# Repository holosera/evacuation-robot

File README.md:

evacuation-robot
================

Robot for automated evacuation of exetainer vials used in research.

Frame (acrylic sheets)

3d Printed mechanical parts 

Custom electronics (pcb and schematics)

Additional parts list

Filetypes:
.scad -> Openscad

.svg -> Inkscape

.ino -> Arduino IDE

.dxf -> Inkscape

.stl -> Meshlab

.brd -> Eagle

.sch -> Eagle

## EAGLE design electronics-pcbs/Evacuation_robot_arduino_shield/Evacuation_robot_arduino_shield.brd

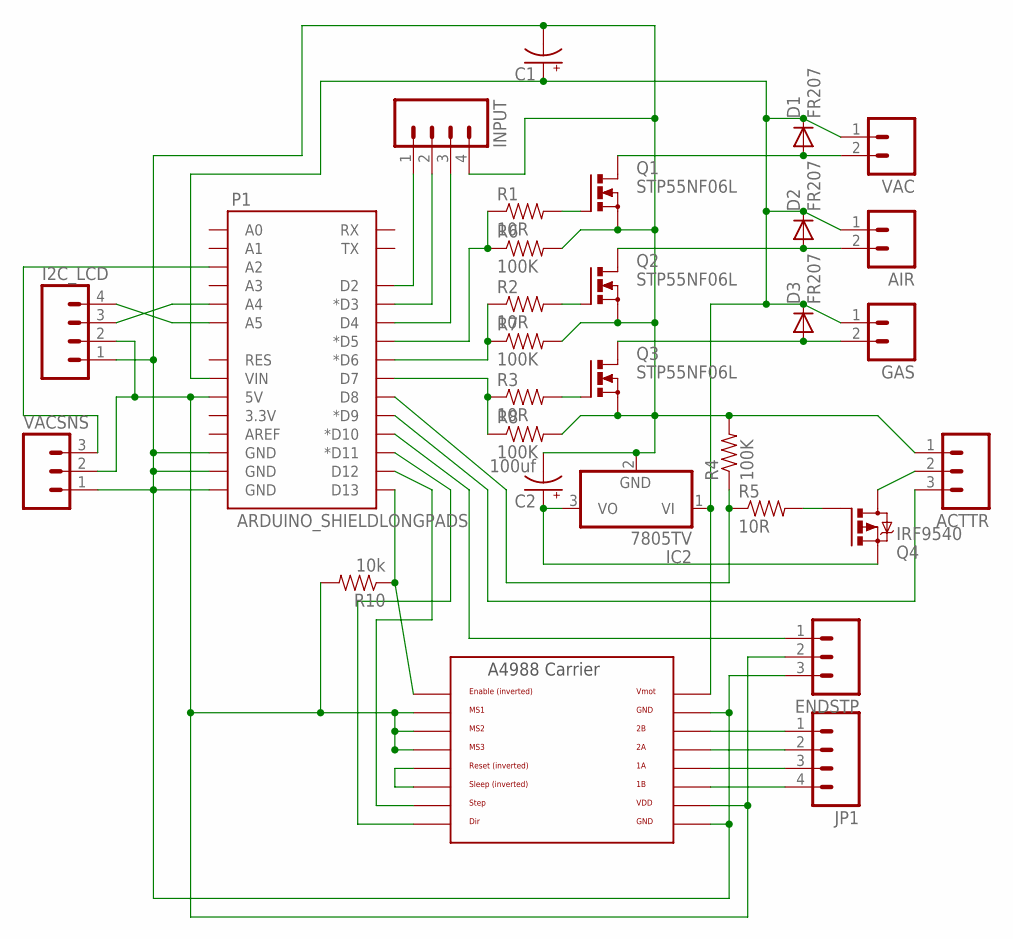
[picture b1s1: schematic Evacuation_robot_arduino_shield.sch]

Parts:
ACTTR: M03LONGPADS; 1X03_LONGPADS
AIR: M02PTH3; 1X02_LONGPADS
C1: CAP_POLPTH4; CPOL-RADIAL-1000UF-25V
C2: 100uf; CPOL-RADIAL-100UF-25V
D1, D2, D3: FR207; DIODE-1N4148
ENDSTP: M03LONGPADS; 1X03_LONGPADS
GAS: M02PTH3; 1X02_LONGPADS
I2C_LCD: M04LONGPADS; 1X04_LONGPADS
IC2: 7805TV; TO220V
INPUT: M04LONGPADS; 1X04_LONGPADS
JP1: M04LONGPADS; 1X04_LONGPADS
P1: ARDUINO_SHIELDLONGPADS; DUEMILANOVE_SHIELD_LONGPADS
Q1, Q2, Q3: STP55NF06L; TO220BV
Q4: IRF9540; TO220BV
R1, R2, R3, R5: 10R; AXIAL-0.3
R4, R6, R7, R8: 100K; AXIAL-0.3
R10: 10k; AXIAL-0.3
U$1: A4988BREAKOUT
VAC: M02PTH3; 1X02_LONGPADS
VACSNS: M03LONGPADS; 1X03_LONGPADS

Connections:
unnamed: INPUT.3, P1.D4
unnamed: INPUT.2, P1.D3 (*D3)
unnamed: P1.D6 (*D6), R2.P$1 (1), R7.P$1 (1)
unnamed: P1.D7, R3.P$1 (1), R8.P$1 (1)
unnamed: P1.D5 (*D5), R1.P$1 (1), R6.P$1 (1)
unnamed: ENDSTP.1, P1.D10 (*D10)
unnamed: Q1.G, R1.P$2 (2)
unnamed: JP1.1, U$1.2B
unnamed: INPUT.1, P1.D2
unnamed: Q3.G, R3.P$2 (2)
unnamed: Q2.G, R2.P$2 (2)
unnamed: D1.A, Q1.D, VAC.2
unnamed: AIR.2, D2.A, Q2.D
unnamed: D3.A, GAS.2, Q3.D
unnamed: I2C_LCD.3, P1.A4
unnamed: JP1.2, U$1.2A
unnamed: I2C_LCD.4, P1.A5
unnamed: AIR.1, C1.1 (+), D1.C, D2.C, D3.C, GAS.1, IC2.1 (VI), P1.VIN, U$1.VMOT, VAC.1
unnamed: JP1.3, U$1.1A
unnamed: JP1.4, U$1.1B
unnamed: U$1.RST, U$1.SLP (SLEEP)
unnamed: ACTTR.3, P1.D9 (*D9)
unnamed: Q4.G, R5.P$2 (2)
unnamed: P1.D13, R10.P$1 (1), U$1.EN
unnamed: P1.D11 (*D11), U$1.DIR
unnamed: P1.D8, R4.P$1 (1), R5.P$1 (1)
unnamed: P1.A2, VACSNS.3
unnamed: C2.1 (+), IC2.3 (VO), Q4.S
unnamed: P1.D12, U$1.STEP
unnamed: ACTTR.2, Q4.D
unnamed: ENDSTP.2, I2C_LCD.2, P1.5V, R10.P$2 (2), U$1.MS1, U$1.MS2, U$1.MS3, U$1.VDD, VACSNS.2
unnamed: ACTTR.1, C1.2 (-), C2.2 (-), ENDSTP.3, I2C_LCD.1, IC2.2 (GND), INPUT.4, P1.GND@0 (GND), P1.GND@1 (GND), P1.GND@2 (GND), Q1.S, Q2.S, Q3.S, R4.P$2 (2), R6.P$2 (2), R7.P$2 (2), R8.P$2 (2), U$1.GND, U$1.GND@0 (GND), VACSNS.1

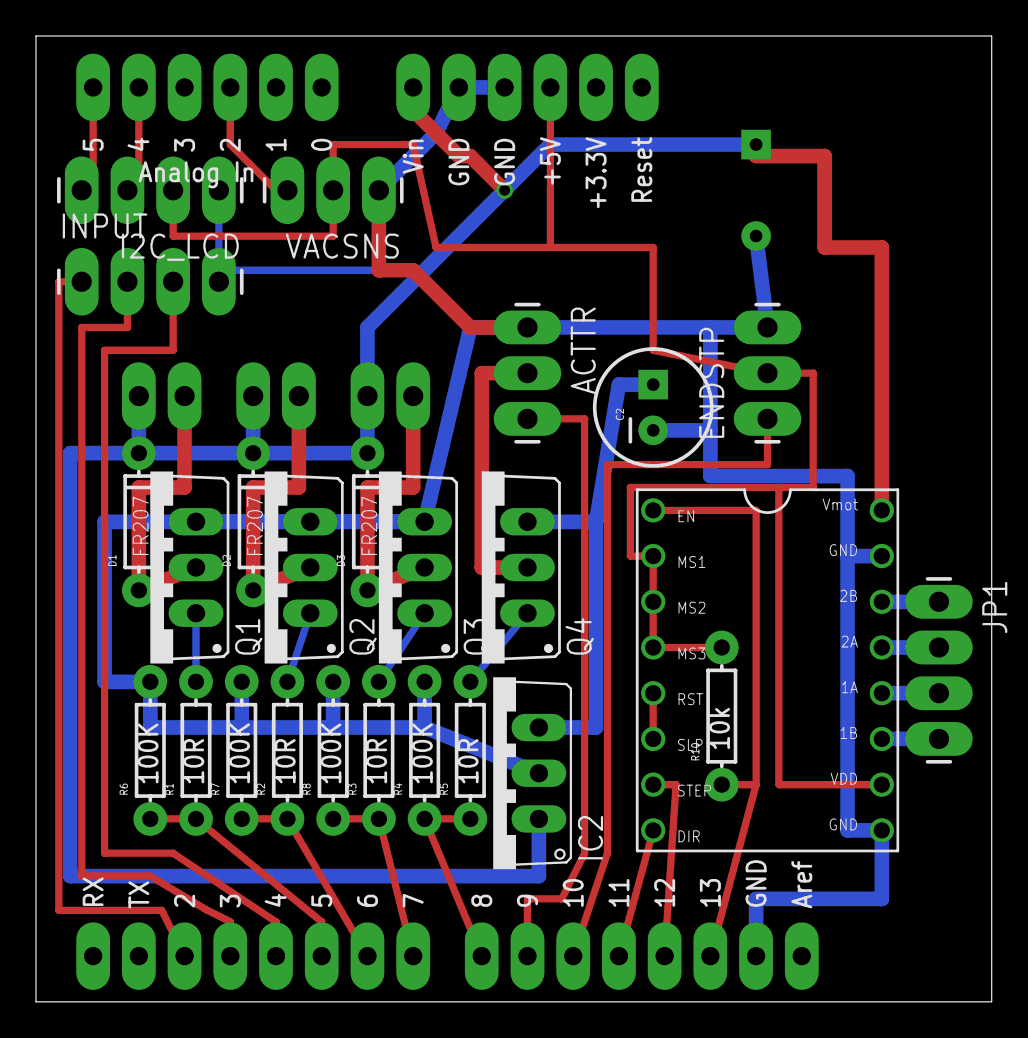
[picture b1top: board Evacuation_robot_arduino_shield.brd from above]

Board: 2 copper layers, 53.1 x 53.7 mm, 30 parts (1 on the bottom side), 32 nets.

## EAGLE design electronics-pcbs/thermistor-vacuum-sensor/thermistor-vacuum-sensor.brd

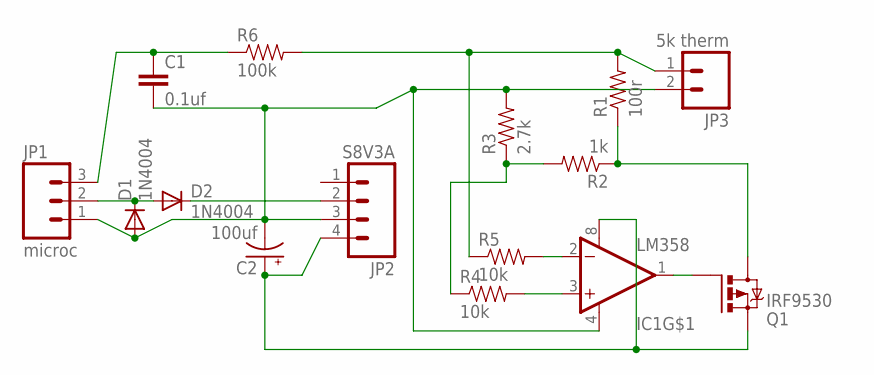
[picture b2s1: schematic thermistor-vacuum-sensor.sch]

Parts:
C1: 0.1uf; CAP-PTH-SMALL
C2: 100uf; CPOL-RADIAL-100UF-25V
D1, D2: 1N4004; DO41-10
IC1: LM358; DIP08
JP1: microc; 1X03_LONGPADS
JP2: S8V3A; 1X04_LONGPADS
JP3: 5k therm; 1X02_LOCK_LONGPADS
Q1: IRF9530; TO220BV
R1: 100r; AXIAL-0.3
R2: 1k; AXIAL-0.3
R3: 2.7k; AXIAL-0.3
R4, R5: 10k; AXIAL-0.3
R6: 100k; AXIAL-0.3

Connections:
unnamed: D1.C, D2.A, JP1.2
unnamed: D2.C, JP2.2
unnamed: C1.2, C2.2 (-), D1.A, IC1.4 (V-), JP1.1, JP2.3, JP3.2, R3.P$2 (2)
unnamed: C2.1 (+), IC1.8 (V+), JP2.4, Q1.S
unnamed: C1.1, JP1.3, R6.P$1 (1)
unnamed: IC1.2 (-IN), R5.P$2 (2)
unnamed: IC1.3 (+IN), R4.P$2 (2)
unnamed: IC1.1 (OUT), Q1.G
unnamed: JP3.1, R1.P$2 (2), R5.P$1 (1), R6.P$2 (2)
unnamed: R2.P$2 (2), R3.P$1 (1), R4.P$1 (1)
unnamed: Q1.D, R1.P$1 (1), R2.P$1 (1)

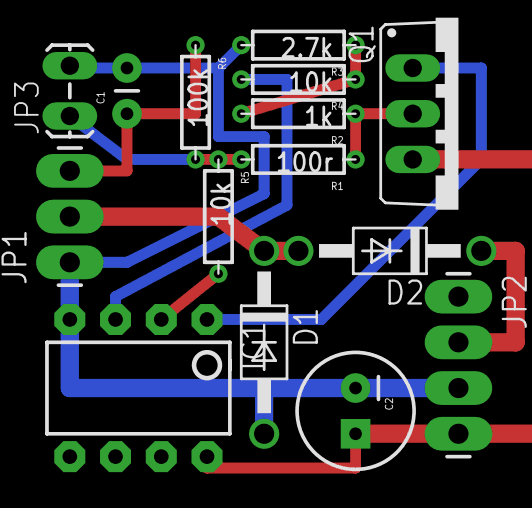
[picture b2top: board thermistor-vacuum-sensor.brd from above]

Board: 2 copper layers, 15 parts (0 on the bottom side), 11 nets.

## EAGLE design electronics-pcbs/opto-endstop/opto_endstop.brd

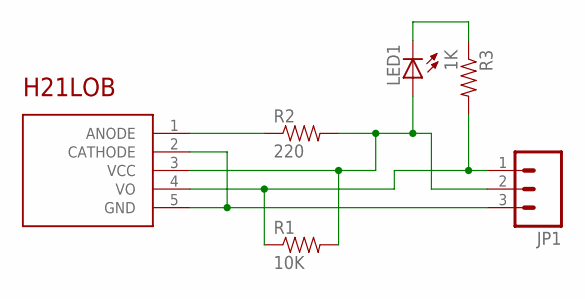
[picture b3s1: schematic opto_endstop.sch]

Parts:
JP1: M03LONGPADS; 1X03_LONGPADS
LED1: LED5MM
R1: 10K; AXIAL-0.3
R2: 220; AXIAL-0.3
R3: 1K; AXIAL-0.3
U$2: H21LOB; H21

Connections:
unnamed: R2.P$1 (1), U$2.1 (ANODE)
unnamed: JP1.2, LED1.A, R1.P$2 (2), R2.P$2 (2), U$2.3 (VCC)
unnamed: JP1.3, U$2.2 (CATHODE), U$2.5 (GND)
unnamed: JP1.1, R1.P$1 (1), R3.P$2 (2), U$2.4 (VO)
unnamed: LED1.K (C), R3.P$1 (1)

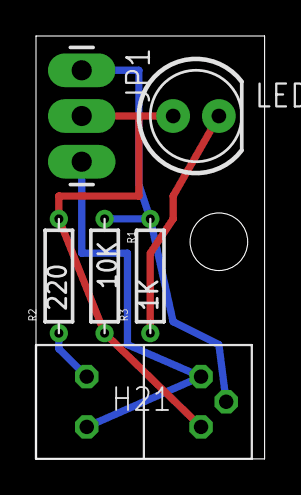
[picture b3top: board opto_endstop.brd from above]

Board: 2 copper layers, 12.7 x 23.5 mm, 6 parts (0 on the bottom side), 5 nets.

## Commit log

2014-05-03 added 3d printed parts
    3d printed parts for evacuation-robot
2014-05-03 added parts
2014-05-03 added parts and source code
2014-06-05 Updated front plate and sled for added rigidity
    more solid design and added adjustability of needle depth
2014-06-05 Changes to sled and front plate
    More solid design

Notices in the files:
parts and their libraries:
SparkFun-Connectors: Licensing: CC v3.0 Share-Alike You are welcome to use this library for commercial purposes.
